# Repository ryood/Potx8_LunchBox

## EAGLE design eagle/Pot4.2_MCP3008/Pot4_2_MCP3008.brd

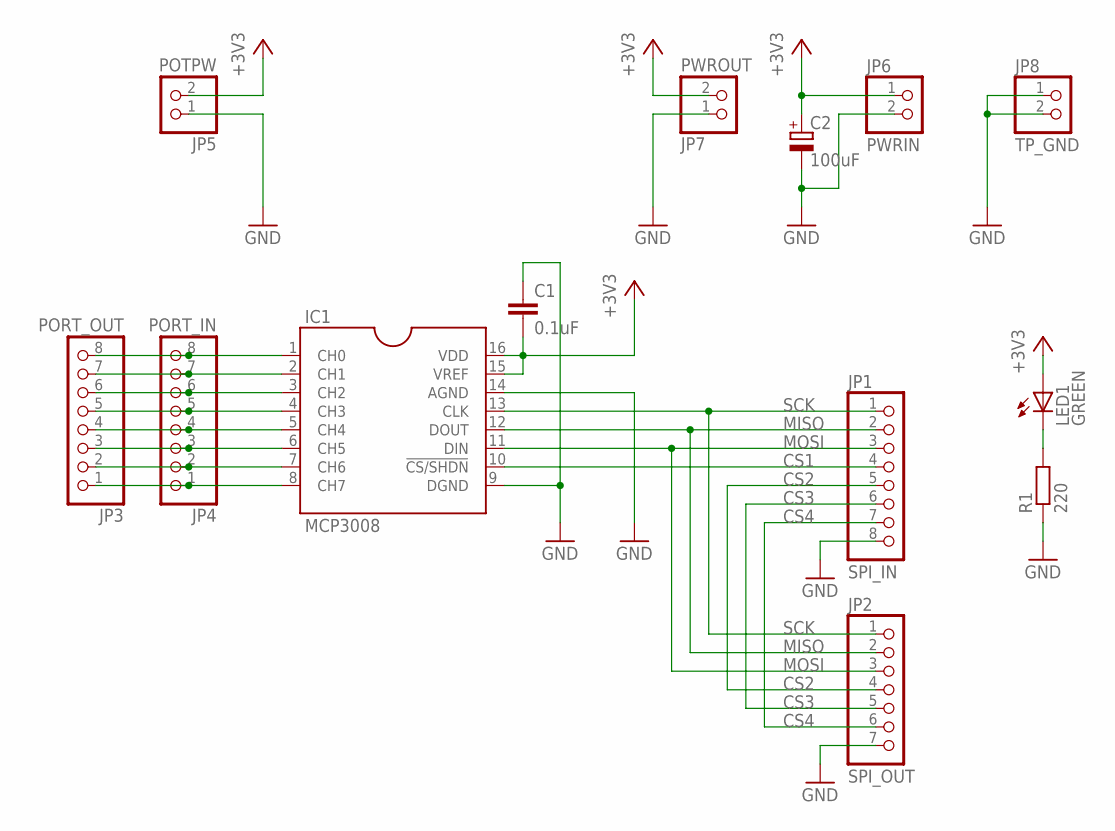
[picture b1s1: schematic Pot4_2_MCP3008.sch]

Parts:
C1: 0.1uF; C025-024X044
C2: 100uF; E2,5-7
IC1: MCP3008
JP1: SPI_IN; 1X08/90
JP2: SPI_OUT; 1X07/90
JP3: PORT_OUT; 1X08
JP4: PORT_IN; 1X08/90
JP5: POTPW; 1X02/90
JP6: PWRIN; 1X02/90
JP7: PWROUT; 1X02/90
JP8: TP_GND; 1X02
LED1: GREEN; LED3MM
R1: 220; 0207/7

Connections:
+3V3: C1.2, C2.+, IC1.15 (VREF), IC1.16 (VDD), JP5.2, JP6.1, JP7.2, LED1.A
CS1: IC1.10 (!CS/SHDN), JP1.4
CS2: JP1.5, JP2.4
CS3: JP1.6, JP2.5
CS4: JP1.7, JP2.6
GND: C1.1, C2.-, IC1.9 (DGND), IC1.14 (AGND), JP1.8, JP2.7, JP5.1, JP6.2, JP7.1, JP8.1, JP8.2, R1.1
MISO: IC1.12 (DOUT), JP1.2, JP2.2
MOSI: IC1.11 (DIN), JP1.3, JP2.3
unnamed: IC1.1 (CH0), JP3.8, JP4.8
unnamed: IC1.2 (CH1), JP3.7, JP4.7
unnamed: IC1.3 (CH2), JP3.6, JP4.6
unnamed: IC1.4 (CH3), JP3.5, JP4.5
unnamed: IC1.5 (CH4), JP3.4, JP4.4
unnamed: IC1.6 (CH5), JP3.3, JP4.3
unnamed: IC1.7 (CH6), JP3.2, JP4.2
unnamed: IC1.8 (CH7), JP3.1, JP4.1
unnamed: LED1.K (C), R1.2
SCK: IC1.13 (CLK), JP1.1, JP2.1

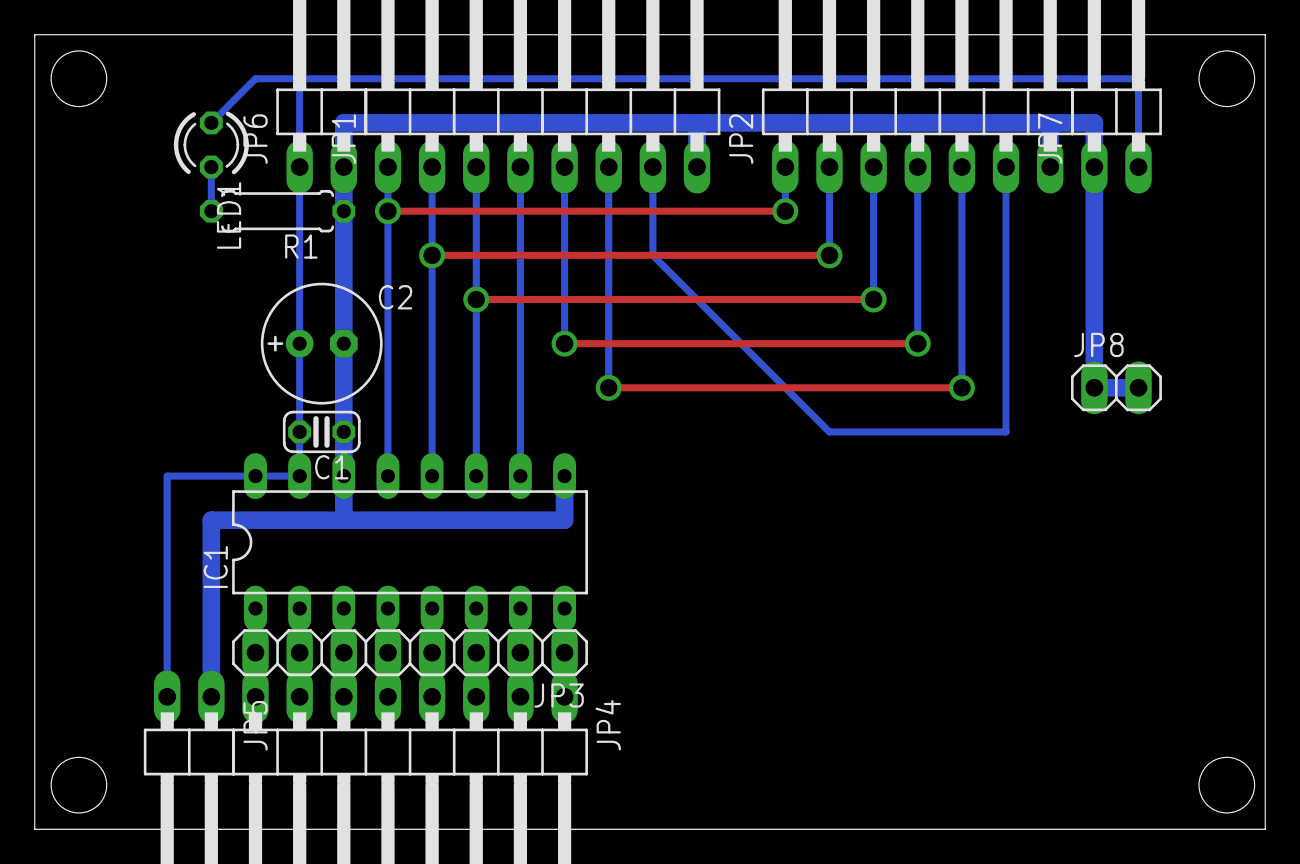
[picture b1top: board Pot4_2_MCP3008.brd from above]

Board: 2 copper layers, 70.8 x 45.7 mm, 13 parts (0 on the bottom side), 18 nets.

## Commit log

2017-11-03 Add Chassis Design files
2017-12-03 Side Panel
